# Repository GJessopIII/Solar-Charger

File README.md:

# Solar-Charger
Documentation is located [here](https://solar-charger.rtfd.io)

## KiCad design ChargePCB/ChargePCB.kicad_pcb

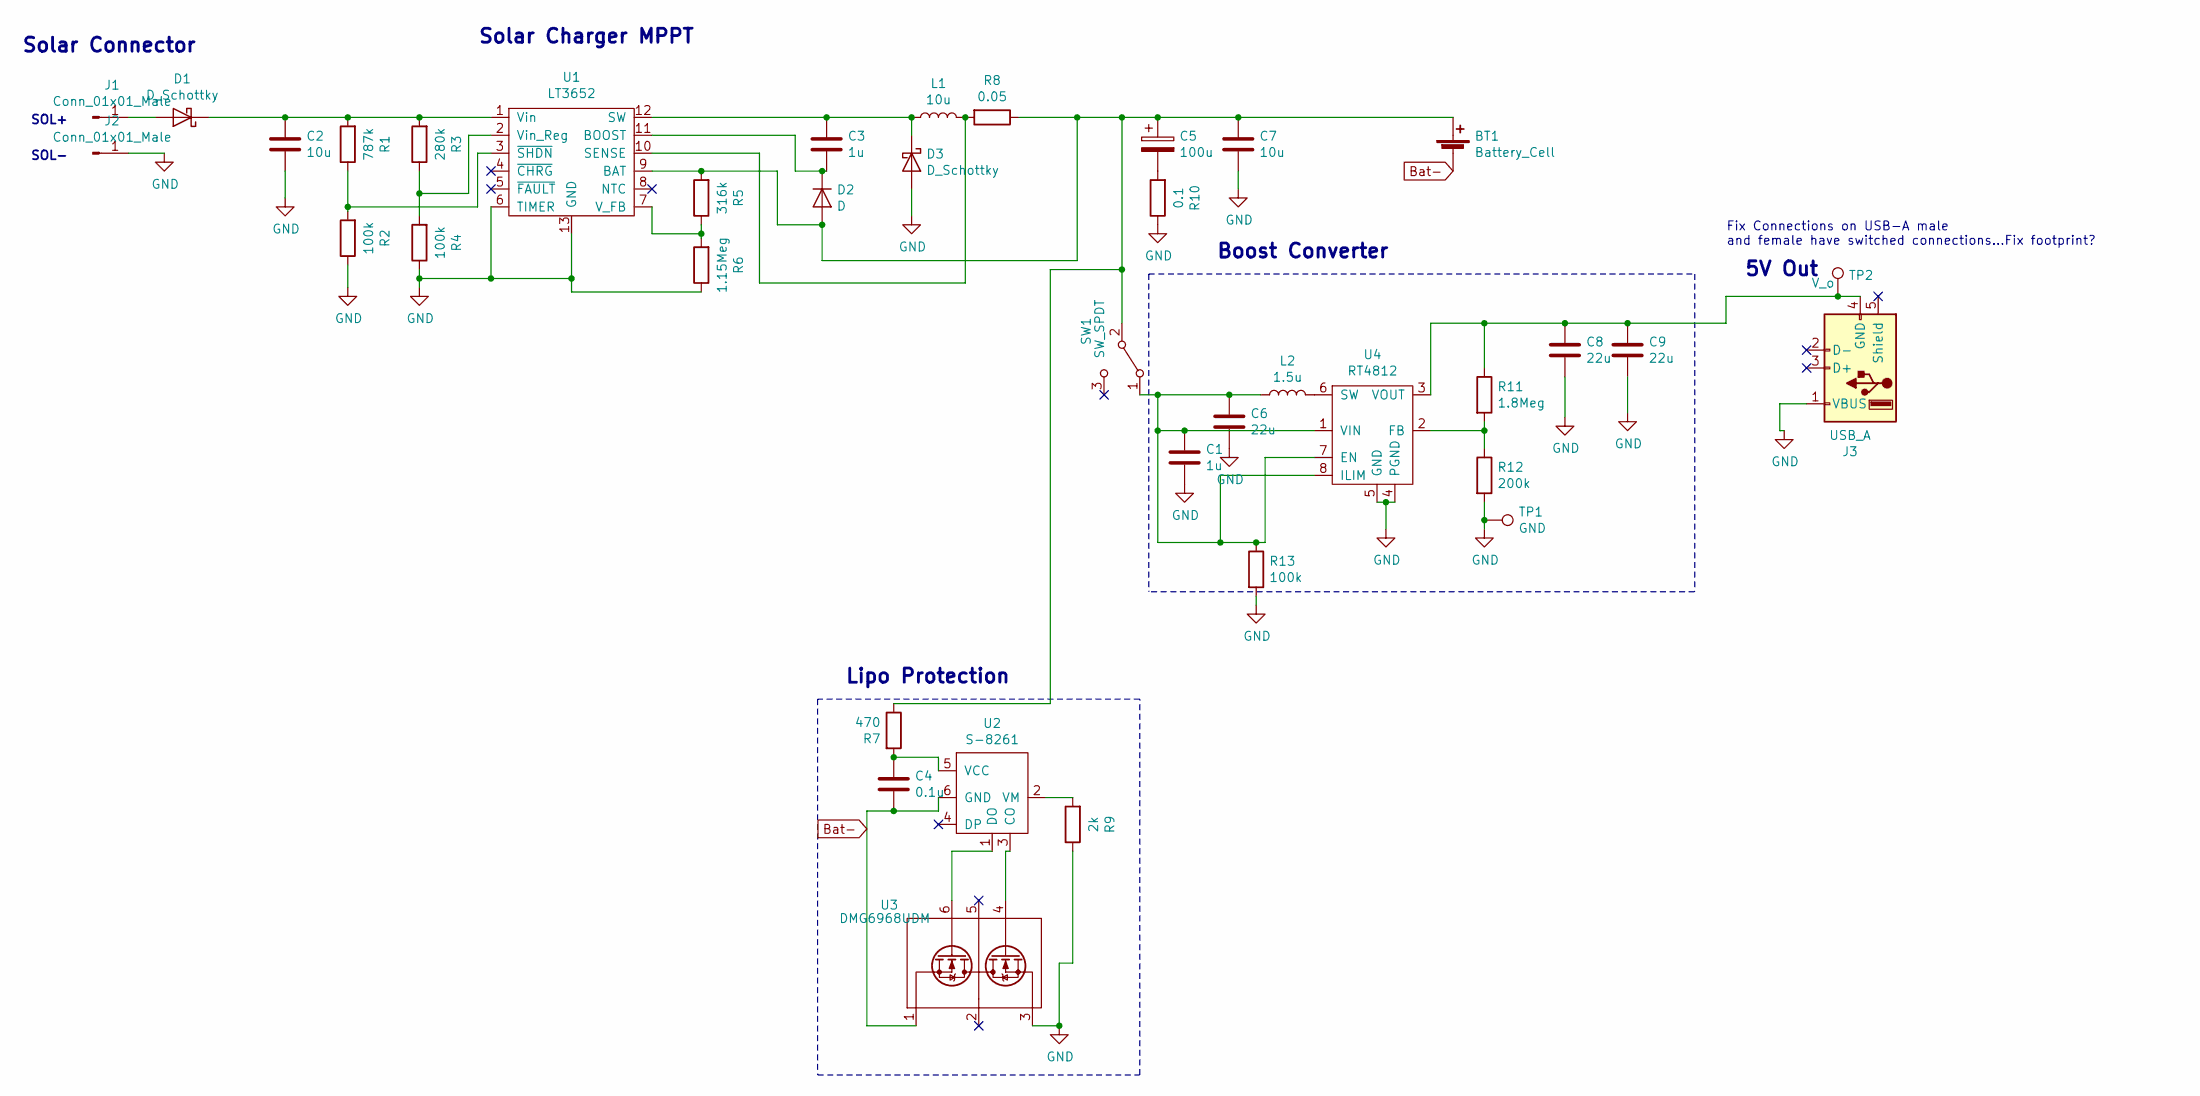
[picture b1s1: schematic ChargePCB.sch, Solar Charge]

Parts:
BT1: Battery_Cell; BatteryHolder_MPD_BH-18650-PC2
C1, C3: 1u; C_0805_2012Metric
C2, C7: 10u; C_0805_2012Metric
C4: 0.1u; C_0805_2012Metric
C5: 100u; CP_Elec_6.3x5.4_Nichicon
C6, C8, C9: 22u; C_0805_2012Metric
D1, D3: D_Schottky; D_SMC
D2: D; D_SOD-323F
J1, J2: Conn_01x01_Male; SolderWirePad_1x01_Drill0.8mm
J3: USB_A; USB_A_CNCTech_1001-011-01101_Horizontal
L1: 10u; L_Axial_L20.0mm_D8.0mm_P5.08mm_Vertical
L2: 1.5u; L_Bourns-SRN6028
R1: 787k; R_0805_2012Metric
R2, R4, R13: 100k; R_0805_2012Metric
R3: 280k; R_0805_2012Metric
R5: 316k; R_0805_2012Metric
R6: 1.15Meg; R_0805_2012Metric
R7: 470; R_0805_2012Metric
R8: 0.05; R_0805_2012Metric
R9: 2k; R_0805_2012Metric
R10: 0.1; R_0805_2012Metric
R11: 1.8Meg; R_0805_2012Metric
R12: 200k; R_0805_2012Metric
SW1: SW_SPDT; SW_SPDT_PCM12
TP1: GND; TestPoint_Plated_Hole_D2.0mm
TP2: V_o; TestPoint_Plated_Hole_D2.0mm
U1: LT3652; MSOP-12-1EP_3x4mm_P0.65mm_EP1.65x2.85mm
U2: S-8261; SOT-23-6
U3: DMG6968UDM; SOT-23-6
U4: RT4812; TSOT-23-8

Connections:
Bat-: BT1.2 (-), C4.2, U2.6 (GND), U3.1
GND: C1.2, C2.2, C6.2, C7.2, C8.2, C9.2, D3.2 (A), J2.1, J3.1 (VBUS), R2.1, R4.1, R6.1, R9.1, R10.1, R12.2, R13.2, TP1.1, U1.6 (TIMER), U1.13 (GND), U3.3, U4.4 (PGND), U4.5 (GND)
unnamed: BT1.1 (+), C5.1, C7.1, D2.2 (A), R5.2, R7.1, R8.1, SW1.2 (B), U1.9 (BAT)
unnamed: C1.1, C6.1, L2.1, R13.1, SW1.1 (A), U4.1 (VIN), U4.7 (EN), U4.8 (ILIM)
unnamed: C2.1, D1.1 (K), R1.2, R3.2, U1.1 (Vin)
unnamed: C3.1, D3.1 (K), L1.1, U1.12 (SW)
unnamed: C3.2, D2.1 (K), U1.11 (BOOST)
unnamed: C4.1, R7.2, U2.5 (VCC)
unnamed: C5.2, R10.2
unnamed: C8.1, C9.1, J3.4 (GND), R11.1, TP2.1, U4.3 (VOUT)
unnamed: D1.2 (A), J1.1
unnamed: L1.2, R8.2, U1.10 (SENSE)
unnamed: L2.2, U4.6 (SW)
unnamed: R1.1, R2.2, U1.3 (~SHDN)
unnamed: R3.1, R4.2, U1.2 (Vin_Reg)
unnamed: R5.1, R6.2, U1.7 (V_FB)
unnamed: R9.2, U2.2 (VM)
unnamed: R11.2, R12.1, U4.2 (FB)
unnamed: U2.1 (DO), U3.6
unnamed: U2.3 (CO), U3.4

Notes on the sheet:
Boost Converter
Solar Charger MPPT
SOL+
SOL-
5V Out
Lipo Protection
Solar Connector
Fix Connections on USB-A male and female have switched connections...Fix footprint?

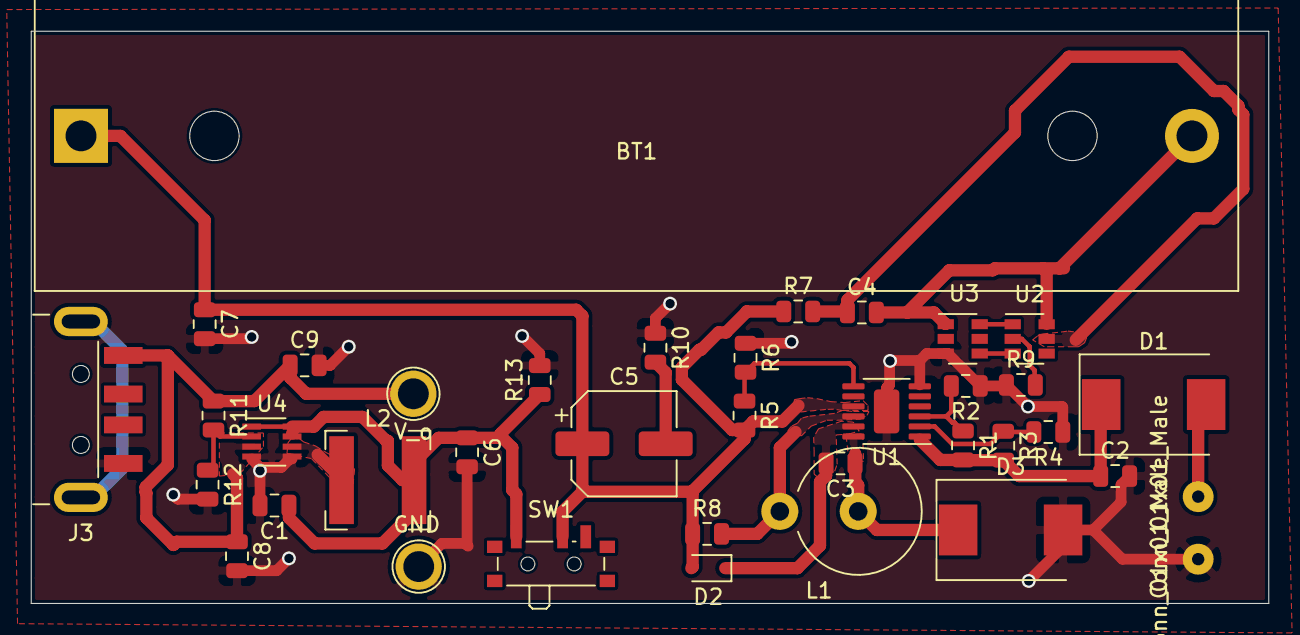
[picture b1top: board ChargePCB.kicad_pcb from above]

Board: 2 copper layers, 80.2 x 37.1 mm, 38 parts (0 on the bottom side), 20 nets.

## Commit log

2019-05-17 Moving everything over from my school Github
2019-05-17 Adding gitignores
2019-05-17 changed silkscreen to say new repository
2019-05-22 Adding docs
2019-05-22 ReadtheDocs
2019-05-23 Changing theme
2019-05-23 MATHHHHH
2019-05-23 Finally starting the things
2019-05-23 testing
2019-05-23 From laptop
2019-05-23 Done for today
2019-05-29 Fixed zone priority issues
2019-06-02 Adding more documentation
2019-06-02 Documentation
2019-06-03 Adding pictures to Troubleshooting page
2019-06-03 Fixing USB polarity, Lipo Protection, and 1.5uH footprint error
2019-06-04 Rev1.1
2019-06-04 More math
2019-06-04 Finished the maths
2019-06-04 changed some wording on index page
2019-06-04 Rewording some stuff
2019-06-06 Added a lot to design section of documentation
2019-06-06 Fixing headers and adding moar
2019-06-09 Adding in results to documentation
2019-06-09 Fixing spelling mistake
2019-06-09 Removing the examples from the index page
